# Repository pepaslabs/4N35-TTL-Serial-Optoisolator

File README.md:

# 4N35-TTL-Serial-Optoisolator
A board for isolating a TTL serial RX / TX pair using 4N35 (6-pin) optoisolators.

# Status

This board is untested.

# Design

See [Designing a TTL Serial Opto isolator](https://github.com/pepaslabs/Electronics/wiki/Designing-a-TTL-Serial-Opto-isolator)

# Board design v1

Initial board design.

## Gerbers

[gerbers.zip](releases/v1/gerbers.zip)

## Schematic

[PDF](releases/v1/4N35-TTL-Serial-Optoisolator%20schematic.pdf).

# License

This board design is [Open-Source Hardware](http://www.oshwa.org/definition/).  It is licensed under the [MIT License](http://opensource.org/licenses/MIT).  It was designed by Jason Pepas.

# Related designs

- https://github.com/pepaslabs/6N137-TTL-Serial-Optoisolator
- https://github.com/pepaslabs/817-TTL-Serial-Optoisolator

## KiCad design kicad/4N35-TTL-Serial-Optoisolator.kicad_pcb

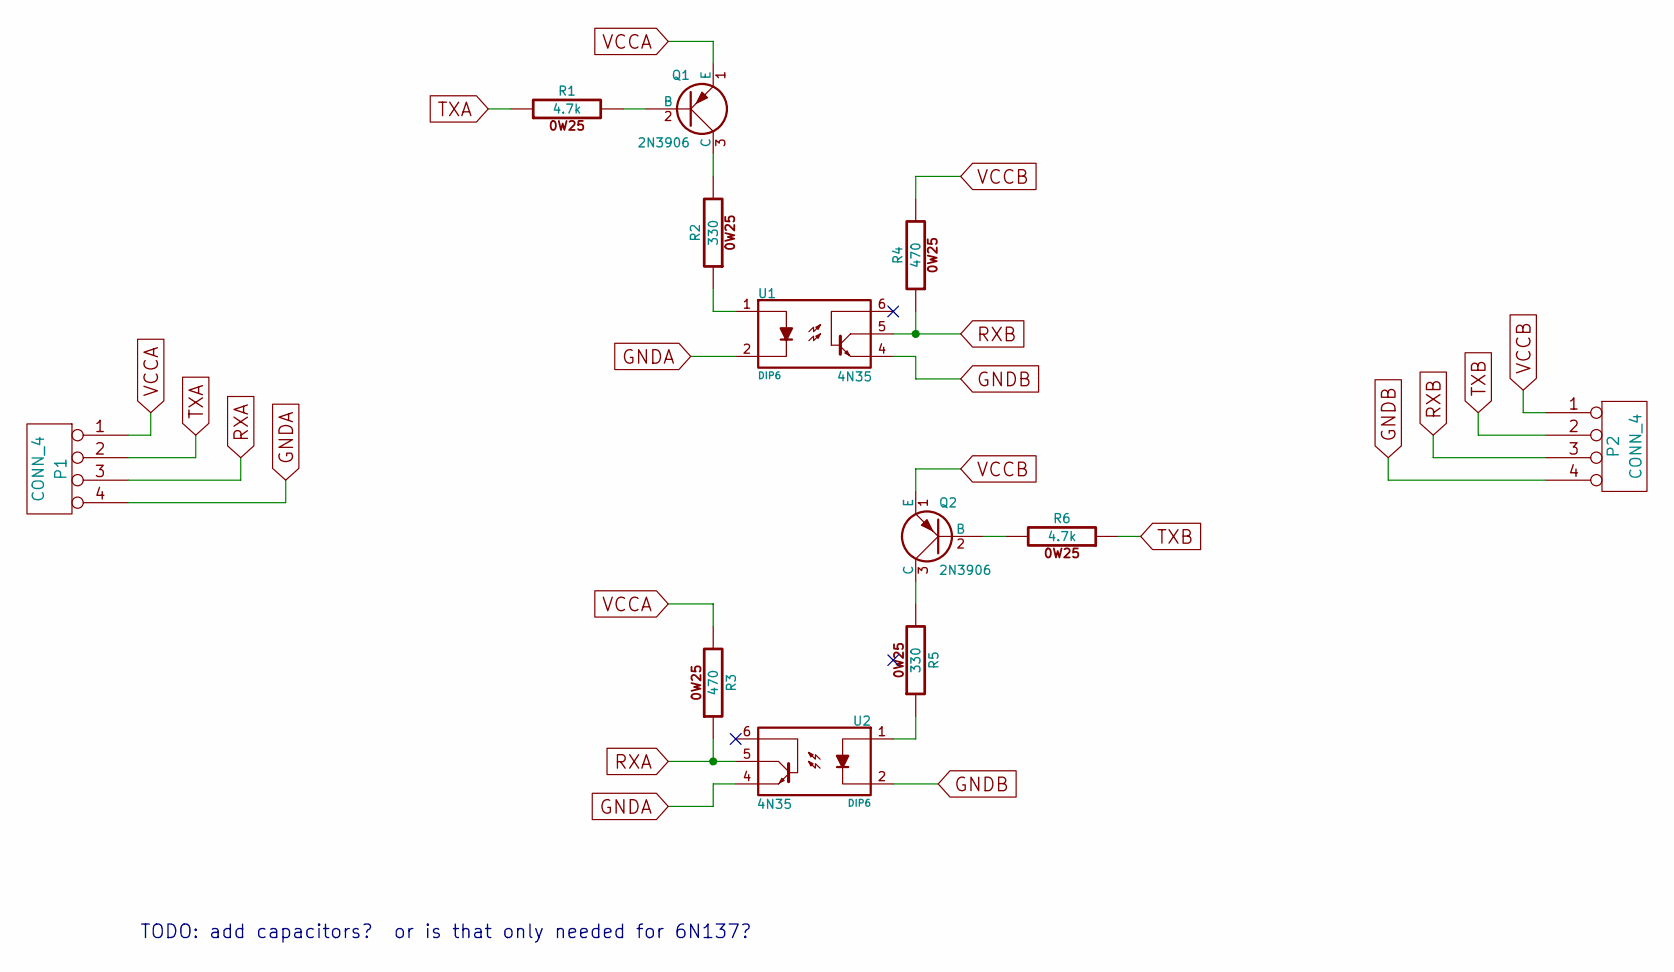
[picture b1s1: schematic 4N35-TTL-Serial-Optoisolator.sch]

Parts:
P1, P2: CONN_4
Q1, Q2: 2N3906
R1, R6: 4.7k
R2, R5: 330
R3, R4: 470
U1, U2: 4N35; DIP6

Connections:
GNDA: P1.4, U1.2, U2.4
GNDB: P2.4, U1.4, U2.2
unnamed: Q2.2 (B), R6.2
unnamed: Q2.3 (C), R5.2
unnamed: R5.1, U2.1
unnamed: Q1.3 (C), R2.2
unnamed: Q1.2 (B), R1.2
unnamed: R2.1, U1.1
RXA: P1.3, R3.1, U2.5
RXB: P2.3, R4.1, U1.5
TXA: P1.2, R1.1
TXB: P2.2, R6.1
VCCA: P1.1, Q1.1 (E), R3.2
VCCB: P2.1, Q2.1 (E), R4.2

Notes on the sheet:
TODO: add capacitors? or is that only needed for 6N137?

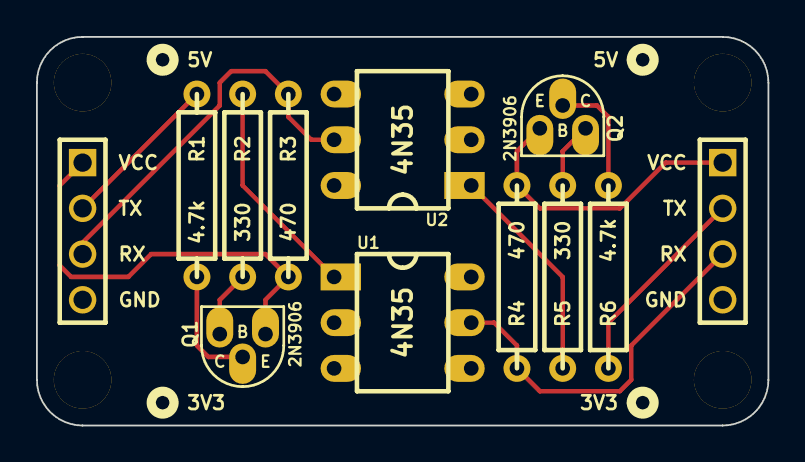
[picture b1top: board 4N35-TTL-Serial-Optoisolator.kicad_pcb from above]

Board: 2 copper layers, 40.6 x 21.6 mm, 16 parts (0 on the bottom side), 14 nets.

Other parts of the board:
H***: Val**; hole_M3_2
H***#2, H***#3, H***#4: Val**; hole_M3_2

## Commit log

2015-05-04 initial import
2015-05-05 fattening traces to 20 mil
2015-05-05 fixing silkscreen text
2015-05-05 adding screenshots
2017-04-22 updating readme
